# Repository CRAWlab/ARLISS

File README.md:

### ARLISS at UL Lafayette
This repository contains code for the [UL Lafayette](http://louisiana.edu) entries into the [ARLISS competition](http://arliss.org).

More information UL Lafayette effort from 2016 can be found on the [CRAWLAB website](http://www.ucs.louisiana.edu/~jev9637/research/ARLISS.html).

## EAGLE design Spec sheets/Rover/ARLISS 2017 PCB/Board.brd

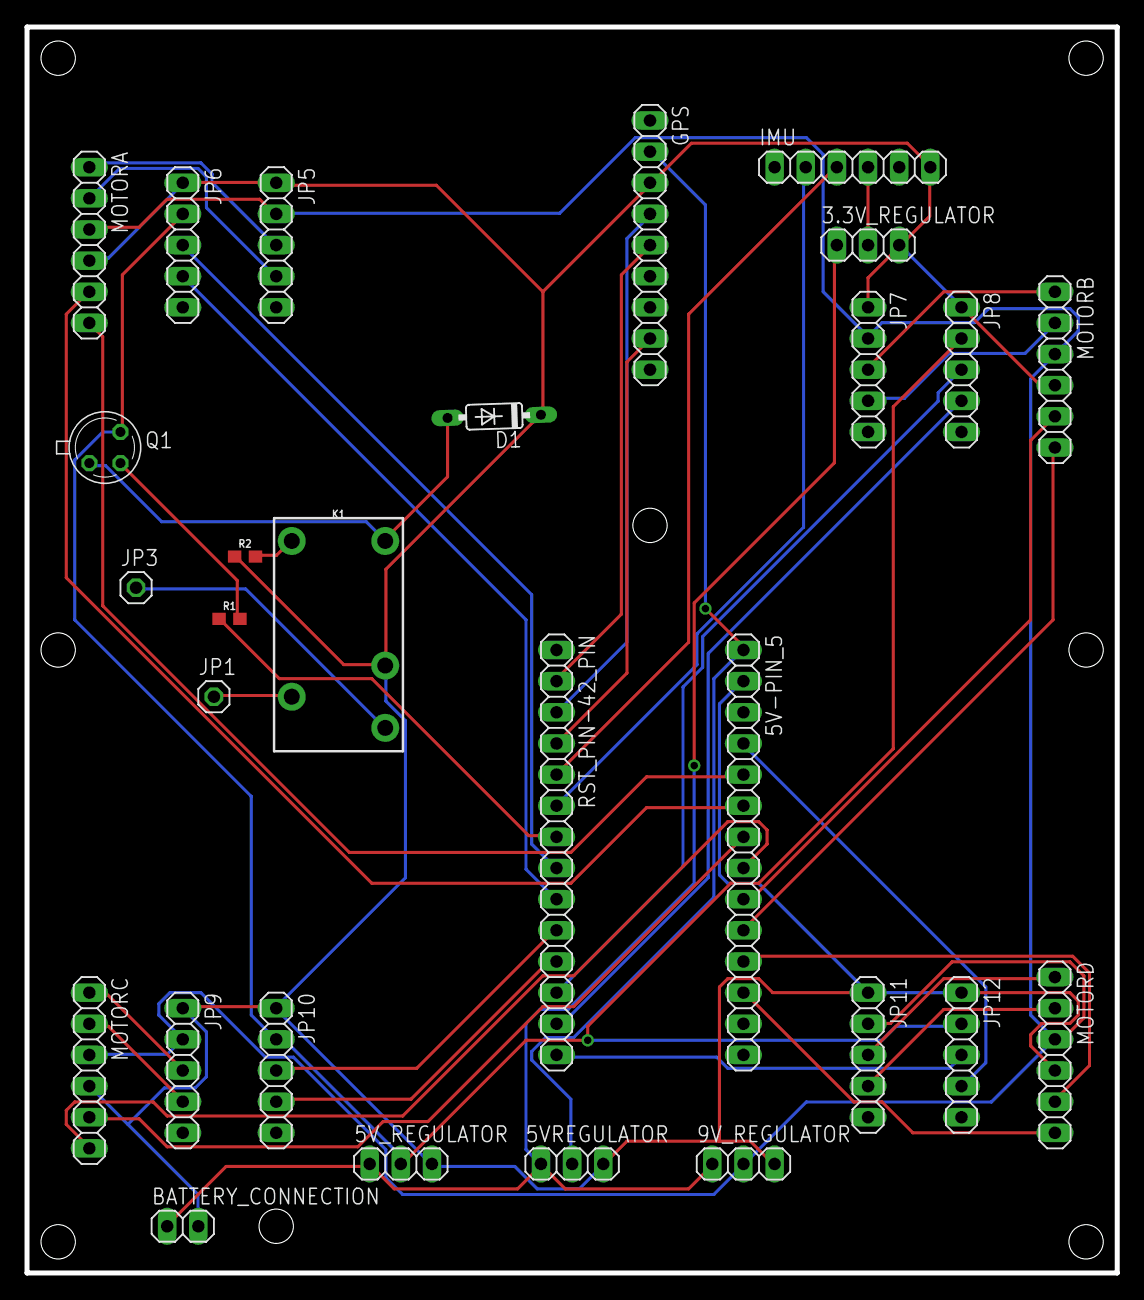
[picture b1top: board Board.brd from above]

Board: 2 copper layers, 88.9 x 101.6 mm, 28 parts (0 on the bottom side), 41 nets.

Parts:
3.3V_REGULATOR, 5VREGULATOR, 5V_REGULATOR, 9V_REGULATOR: 1X03
5V-PIN_5: 1X14
BATTERY_CONNECTION: 1X02
D1: 1N4148DO35-7; DO35-7
GPS: 1X09
IMU: 1X06
JP1, JP3: 1X01
JP5, JP6, JP7, JP8, JP9, JP10, JP11, JP12: 1X05
K1: RELAY-SPDT-JZC-11F; RELAY-JZC
MOTORA: 1X06
MOTORB: 1X06
MOTORC: 1X06
MOTORD: 1X06
Q1: 2N2222A; TO18
R1, R2: 330; 0603
RST_PIN-42_PIN: 1X14

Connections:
unnamed: GPS.5, RST_PIN-42_PIN.2
unnamed: GPS.4, RST_PIN-42_PIN.3
unnamed: Q1.2, R1.2
unnamed: R1.1, RST_PIN-42_PIN.7
unnamed: GPS.8, RST_PIN-42_PIN.4
unnamed: IMU.3, RST_PIN-42_PIN.5
unnamed: IMU.2, RST_PIN-42_PIN.6
unnamed: JP6.3, RST_PIN-42_PIN.8
unnamed: JP6.4, RST_PIN-42_PIN.9
unnamed: JP10.3, RST_PIN-42_PIN.10
unnamed: JP10.4, RST_PIN-42_PIN.11
unnamed: JP8.3, RST_PIN-42_PIN.12
unnamed: JP8.4, RST_PIN-42_PIN.13
unnamed: JP12.3, RST_PIN-42_PIN.14
unnamed: 5V-PIN_5.4, JP12.4
unnamed: JP5.3, MOTORA.1
unnamed: 9V_REGULATOR.2, JP5.2, JP7.2, JP9.2, JP11.2, MOTORA.3, MOTORB.3, MOTORC.3, MOTORD.3
unnamed: 5V-PIN_5.7, MOTORC.5
unnamed: JP9.4, MOTORC.2
unnamed: 5V-PIN_5.8, MOTORC.6
unnamed: 5V-PIN_5.9, MOTORB.5
unnamed: 5V-PIN_5.5, MOTORA.6
unnamed: 5V-PIN_5.6, MOTORA.5
unnamed: 5V-PIN_5.10, MOTORB.6
unnamed: 5V-PIN_5.11, MOTORD.5
unnamed: 5V-PIN_5.12, MOTORD.6
unnamed: JP11.3, MOTORD.1
unnamed: JP11.4, MOTORD.2
unnamed: JP5.4, MOTORA.2
unnamed: K1.1, R2.2
unnamed: D1.A, K1.5, Q1.1
unnamed: 3.3V_REGULATOR.1, 5VREGULATOR.1, 5V_REGULATOR.1, 9V_REGULATOR.1, BATTERY_CONNECTION.1
unnamed: JP7.3, MOTORB.1
unnamed: JP7.4, MOTORB.2
unnamed: JP1.1, K1.4
unnamed: 5V_REGULATOR.2, JP6.2, JP8.2, JP10.2, JP12.2, Q1.3
unnamed: JP3.1, K1.3
unnamed: 5V-PIN_5.1, 5VREGULATOR.2, GPS.2
unnamed: JP9.3, MOTORC.1
unnamed: 3.3V_REGULATOR.2, IMU.4
unnamed: 3.3V_REGULATOR.3, 5V-PIN_5.2, 5VREGULATOR.3, 5V_REGULATOR.3, 9V_REGULATOR.3, BATTERY_CONNECTION.2, D1.C, GPS.3, IMU.6, JP5.1, JP6.1, JP7.1, JP8.1, JP9.1, JP10.1, JP11.1, JP12.1, K1.2, MOTORA.4, MOTORB.4, MOTORC.4, MOTORD.4, R2.1

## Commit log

2015-07-31 Added code from Spring 2015 Senior Design
2015-08-07 Commit of basic PID and geographic calculations
    Includes functions for creating files, doing geographic calculations,
    and a basic PID controller suitable for realtime use
    NOTE: Some parts rely on numPy so they will work as is on the pyboard.
    Conversion to the standard math library is necessary.
2015-08-13 Added BeagleBoneBlack version of SparkFun Motor class
    For the pyboard, will have to change:
    * to Python 3 style print statements
    * GPIO definitions and setup
    * low-level PWM control
2015-08-13 Added script to calculate drop height
2015-09-12 Initial commit of GPS/control visualization
    * Uses Folium to plot trajectory on a map
    * Output is a .html file with interactive information on trajectory
2015-09-15 Added example GPS log file from pyBoard
2015-09-23 GPS visualization
2015-10-25 Create Final.py
    Final program used for rover at ARLISS 2015 competition.
2015-10-25 Create motor.py
    Motor driver program used for Fall 2015 rover. (Written for use with micropyboard and TB6612fng motor driver)
2015-10-25 Create micropyGPS.py
    Pyboard module used for GPS (Adafruit Ultimate GPS.
2016-07-26 Added 2016 folder, reorganized 2015 contest folder
2016-08-29 Moved to Crawlab folder
    Moved the ARLISS files to the Crawlab folder
2016-08-30 Finished Motor Code
    Finished and Tested motor code. Also moved encoder files to the folder.
2016-09-01 Created New motor class file
    Got readings from the encoders and can get out the counts per second
2016-09-01 Added a gitignore
2016-09-01 updated PID code and motor class
2016-09-07 Fixed PID controller, now need to tune
2016-09-08 Tuning PID
2016-09-09 New encoder functions and reorganized main.py
2016-09-09 Finished tuning PID
2016-09-11 Working on the main navigation function
2016-09-12 Setting up XBee for GPS nav testing
2016-09-13 Updates and new files
    Added Pin functions, and added to the main function
2016-09-14 Added Razor IMU convenience class
2016-09-15 Additional Files and Nav Updates
2016-09-22 Added outline of 2016 nav and guidance and draft regular expression for parsing IMU data from SparkFun Razor
2016-10-04 Updated the read_buf and other
2016-10-04 Added md for the nav control and pyboard razor IMU
2017-03-30 Rename Read_Me.txt to Read_Me.md
2017-03-30 Rename Read_Me.md to README.md
2017-04-12 Organization
    Files were all over the place; needed to do some organization.
2017-04-12 Created rover class to simplify main.py
2017-04-16 Main is used to test count
2017-08-10 Add test code for pyboard
2017-08-21 Preperation
    Compiling code/ eliminating bugs
2017-08-23 Adding Robustness
    Pinout established,
    Added functionality for 2 gps,
    Developed PID drive function to be controlled by yaw, still need to
    incorporate encoders, need to test.
2017-08-30 Working on finishing touches
    Split process into final_process and functions to reduce length of
    code. Need to add turning and distance check algorithms.
2017-09-09 Commenting
2017-09-09 Testing/ Commenting/ Organizing
2017-09-09 Commenting/ pushing through
    work_in_progress will eventually become the ‘main.py’ we use in the
    desert
2017-09-10 Commenting/ High level processes
    Need to tune values of PID for:
    functions.cruise_control
    Functions.imu_pid
2017-09-10 Final process completed
    Needs: debugging, commenting, testing
    To-Do: Compile test files for easier debugging/ testing
2017-09-10 tests to tune functions
2017-09-10 Revisions
    Fixed: cruise control
    correct_course_error
    Added: get_location() in functions to reduce main code/ limit errors
2017-09-12 Finishing up
    Added xbee.py for monitoring data via serial
2017-09-12 distance adjustements
    Added abs value for distance comparison in the event that
    functions.calculate_distance returns a negative value.
2017-09-13 Added enable/ disabling of interrupt
2017-09-20 Adding changes from desert
2018-05-02 Added 2018 Folder
2018-05-02 Added link to CRAWLAB ARLISS page from README.md
2018-08-19 Mechanical Folder
    for frame design files etc.
2018-09-08 Configurations file to be put on Pyboard
    Contains all of the variables and misc. setup code.
2018-09-09 added navigation loop/bugs remain
    currently debugging the loop. made changes from the 2017. hopefully a little more clear. not sure if it works yet
2018-09-09 slaughtered some bugs... some remain
    should be working up until it needs to burn the parachute off. correctly detects valid gps data, changes in altitude, and changes in accelerometer
2018-09-09 added changes to update altitude
    now updates the gps before calculating the change in altitude. bugs remain
2018-09-09 removed bugs/cleaned up a few things
    added a few comments to clarify some things, did some general debugging
2018-09-09 added functions file and made other changes
    added the functions file to be put on the pyboard. Added an acceleration and decceleration. added data logging to save the gps locations, altitudes, and other things. added some comments
2018-09-10 added more modules to be put on pyboard
    made changes to imu_pid() function to not do anything if the change in the new_angle and initial angle is within the sensitivity. added the motors module and the razor_imu module
2018-09-10 small debugging
    did some small debugging in configurations, functions, and main_test
2018-09-11 changed parachute burn time because we almost set the robot on fire
    time is now 400 ms.
2018-09-11 uploaded all modules needed on pyboard
    added boot.py, micropyGPS.py, pyboard_PID.py
2018-09-11 added data logging features/LED indicators\comments
    Each data logging instance should include a time stamp in order to get an idea of when each event occurs.
    added LED indicators for when we find the device, we can tell where it is at in the code.
    added comments for clarification.
2018-09-12 finalized data logging
    a few more data logging instances were added and the only thing left to add is a possible better solution to the current imu angle correction and a solution to if the device gets stuck
2018-09-12 Initial list of TODOs inline with code
    This is just the pieces of the code that I think need to be improved. Only very minor changes have been made already.
2018-09-12 Matt made some changes
    matts changes are saved in the on pyboard folder. previous version is in the previous tests folder
2018-09-12 Continued changes in minor formatting and TODOs
2018-09-13 updated the most recent changes from the desert
    placed in the newest code folder
2018-09-13 See TODOs - Minor changes in main and configurations
2018-09-14 Updated GPS visualization for latest version of Folium
2018-09-26 Final From the desert
    Final code and log used in the desert. Contains everything placed on the pyboard

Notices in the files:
parts and their libraries:
SparkFun-Resistors: Licensing: Creative Commons ShareAlike 4.0 International - https://creativecommons.org/licenses/by-sa/4.0
